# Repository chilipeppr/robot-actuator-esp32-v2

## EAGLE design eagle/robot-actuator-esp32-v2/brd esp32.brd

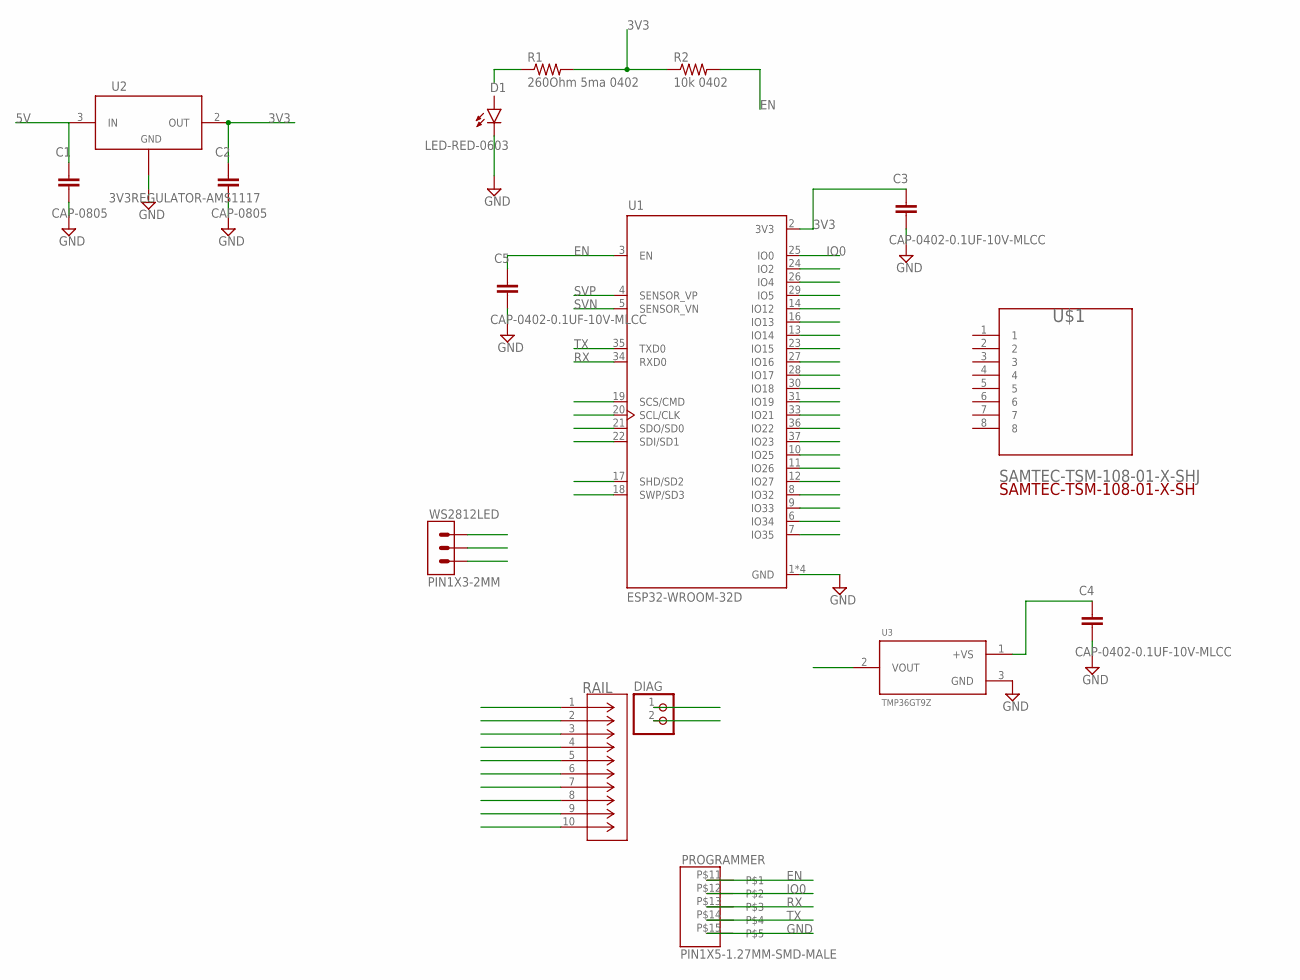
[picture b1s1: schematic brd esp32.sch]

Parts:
C1, C2: CAP-0805; CAP_0805
C3, C4, C5: CAP-0402-0.1UF-10V-MLCC; CAP_0402
D1: LED-RED-0603; LED-0603
DIAG: PINHD-1X2; 1X02
PROGRAMMER: PIN1X5-1.27MM-SMD-MALE; PIN1X5-1.27MM-SMD
R1: 260Ohm 5ma 0402; RES_0402
R2: 10k 0402; RES_0402
RAIL: SSW-105-01-G-D; CON10_2X5_TU_SSQ
U1: ESP32-WROOM-32D; MODULE_ESP32-WROOM-32D
U2: 3V3REGULATOR-AMS1117; SOT-223
U3: TMP36GT9Z; TO127P419X483X533-3P
U$1: SAMTEC-TSM-108-01-X-SHJ; SAMTEC-TSM-108-01-X-SH
WS2812LED: PIN1X3-2MM

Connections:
3V3: C2.1, C3.1, R1.2, R2.1, U1.2 (3V3), U2.2 (OUT), U2.4
5V: C1.1, U2.3 (IN)
EN: C5.1, PROGRAMMER.P$11, R2.2, U1.3 (EN)
GND: C1.2, C2.2, C3.2, C4.2, C5.2, D1.C, PROGRAMMER.P$15, U1.1 (GND), U1.15 (GND), U1.38 (GND), U1.39 (GND), U2.1 (ADJ/GND), U3.3 (GND)
IO0: PROGRAMMER.P$12, U1.25 (IO0)
unnamed: C4.1, U3.1 (+VS)
RX: PROGRAMMER.P$13, U1.34 (RXD0)
SVN: U1.5 (SENSOR_VN)
SVP: U1.4 (SENSOR_VP)
TX: PROGRAMMER.P$14, U1.35 (TXD0)

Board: 2 copper layers, 16 parts (10 on the bottom side), 8 nets, no tracks yet.

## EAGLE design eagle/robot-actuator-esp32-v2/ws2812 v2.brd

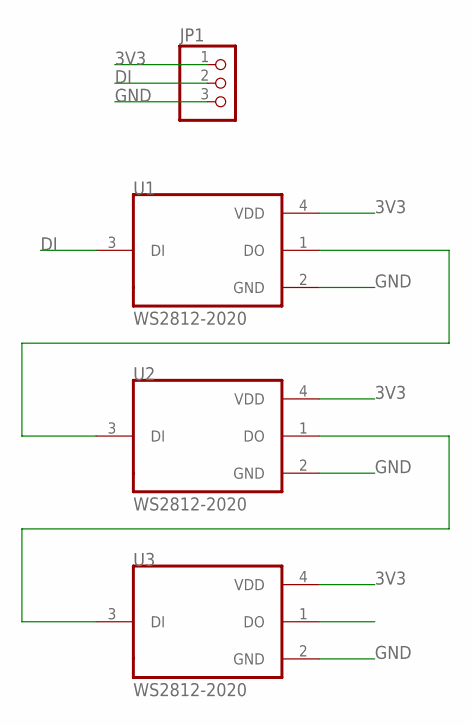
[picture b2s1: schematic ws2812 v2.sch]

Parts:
JP1: PINHD-1X3; 1X03
U1, U2, U3: WS2812-2020; LED_WS2812-2020

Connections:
3V3: JP1.1, U1.4 (VDD), U2.4 (VDD), U3.4 (VDD)
DI: JP1.2, U1.3 (DI)
GND: JP1.3, U1.2 (GND), U2.2 (GND), U3.2 (GND)
unnamed: U1.1 (DO), U2.3 (DI)
unnamed: U2.1 (DO), U3.3 (DI)

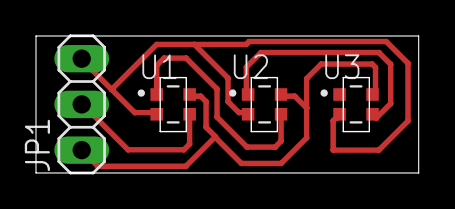
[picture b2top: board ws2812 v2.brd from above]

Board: 2 copper layers, 21.2 x 7.5 mm, 4 parts (0 on the bottom side), 5 nets.

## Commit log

2019-06-17 New boards
2019-06-25 esp32 code
